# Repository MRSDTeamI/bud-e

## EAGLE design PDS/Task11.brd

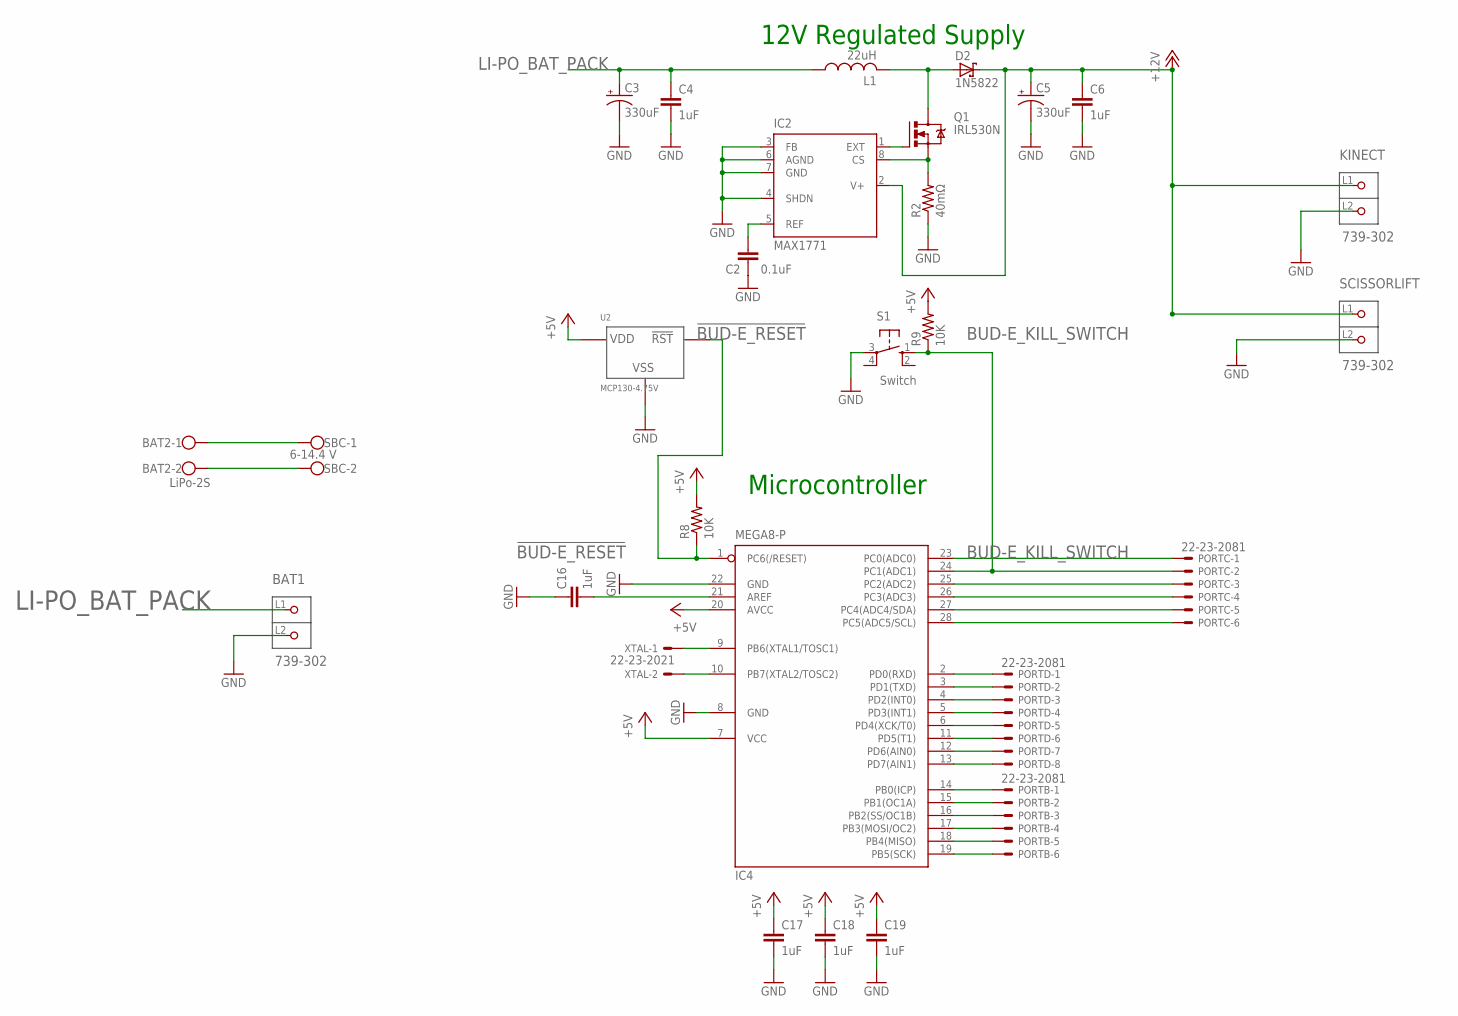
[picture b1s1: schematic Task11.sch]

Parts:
BAT1: 739-302; P-739-302
BAT2: LiPo-2S; W237-113
C2: 0.1uF; C025-025X050
C3, C5: 330uF; E2,5-6
C4, C6, C16, C17, C18, C19: 1uF; C025-025X050
D2: 1N5822; C4111-15
IC2: MAX1771; DIL08
IC4: MEGA8-P; DIL28-3
KINECT: 739-302; P-739-302
L1: 22uH; 0207/15
PORTB: 22-23-2081; 22-23-2061
PORTC: 22-23-2081; 22-23-2061
PORTD: 22-23-2081
Q1: IRL530N; TO220BV
R2: 40mΩ; 0207/12
R8, R9: 10K; 0204/7
S1: Switch; B3F-10XX
SBC: 6-14.4 V; W237-113
SCISSORLIFT: 739-302; P-739-302
U2: MCP130-4.75V; TO92
XTAL: 22-23-2021

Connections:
!BUD-E_RESET: IC4.1 (PC6(/RESET)), R8.1, U2.1 (!RST)
+5V: C17.1, C18.1, C19.1, IC4.7 (VCC), IC4.20 (AVCC), R8.2, R9.2, U2.2 (VDD)
+12V: C5.+, C6.1, D2.C, IC2.2 (V+), KINECT.L1 (P1), SCISSORLIFT.L1 (P1)
BUD-E_KILL_SWITCH: IC4.24 (PC1(ADC1)), PORTC.2, R9.1, S1.1 (S)
GND: BAT1.L2 (P2), C2.1, C3.-, C4.2, C5.-, C6.2, C16.1, C17.2, C18.2, C19.2, IC2.3 (FB), IC2.4 (SHDN), IC2.6 (AGND), IC2.7 (GND), IC4.8 (GND), IC4.22 (GND), KINECT.L2 (P2), R2.1, S1.3, SCISSORLIFT.L2 (P2), U2.3 (VSS)
LI-PO_BAT_PACK: BAT1.L1 (P1), C3.+, C4.1, L1.1
unnamed: IC2.1 (EXT), Q1.G
unnamed: C2.2, IC2.5 (REF)
unnamed: IC2.8 (CS), Q1.S, R2.2
unnamed: IC4.23 (PC0(ADC0)), PORTC.1
unnamed: IC4.25 (PC2(ADC2)), PORTC.3
unnamed: IC4.26 (PC3(ADC3)), PORTC.4
unnamed: D2.A, L1.2, Q1.D
unnamed: IC4.27 (PC4(ADC4/SDA)), PORTC.5
unnamed: IC4.28 (PC5(ADC5/SCL)), PORTC.6
unnamed: IC4.2 (PD0(RXD)), PORTD.1
unnamed: IC4.9 (PB6(XTAL1/TOSC1)), XTAL.1
unnamed: IC4.3 (PD1(TXD)), PORTD.2
unnamed: IC4.4 (PD2(INT0)), PORTD.3
unnamed: IC4.5 (PD3(INT1)), PORTD.4
unnamed: IC4.6 (PD4(XCK/T0)), PORTD.5
unnamed: IC4.11 (PD5(T1)), PORTD.6
unnamed: IC4.12 (PD6(AIN0)), PORTD.7
unnamed: IC4.13 (PD7(AIN1)), PORTD.8
unnamed: IC4.14 (PB0(ICP)), PORTB.1
unnamed: IC4.15 (PB1(OC1A)), PORTB.2
unnamed: IC4.16 (PB2(SS/OC1B)), PORTB.3
unnamed: IC4.17 (PB3(MOSI/OC2)), PORTB.4
unnamed: IC4.18 (PB4(MISO)), PORTB.5
unnamed: IC4.19 (PB5(SCK)), PORTB.6
unnamed: BAT2.1, SBC.1
unnamed: BAT2.2, SBC.2
unnamed: C16.2, IC4.21 (AREF)
unnamed: IC4.10 (PB7(XTAL2/TOSC2)), XTAL.2

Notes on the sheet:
Microcontroller
12V Regulated Supply

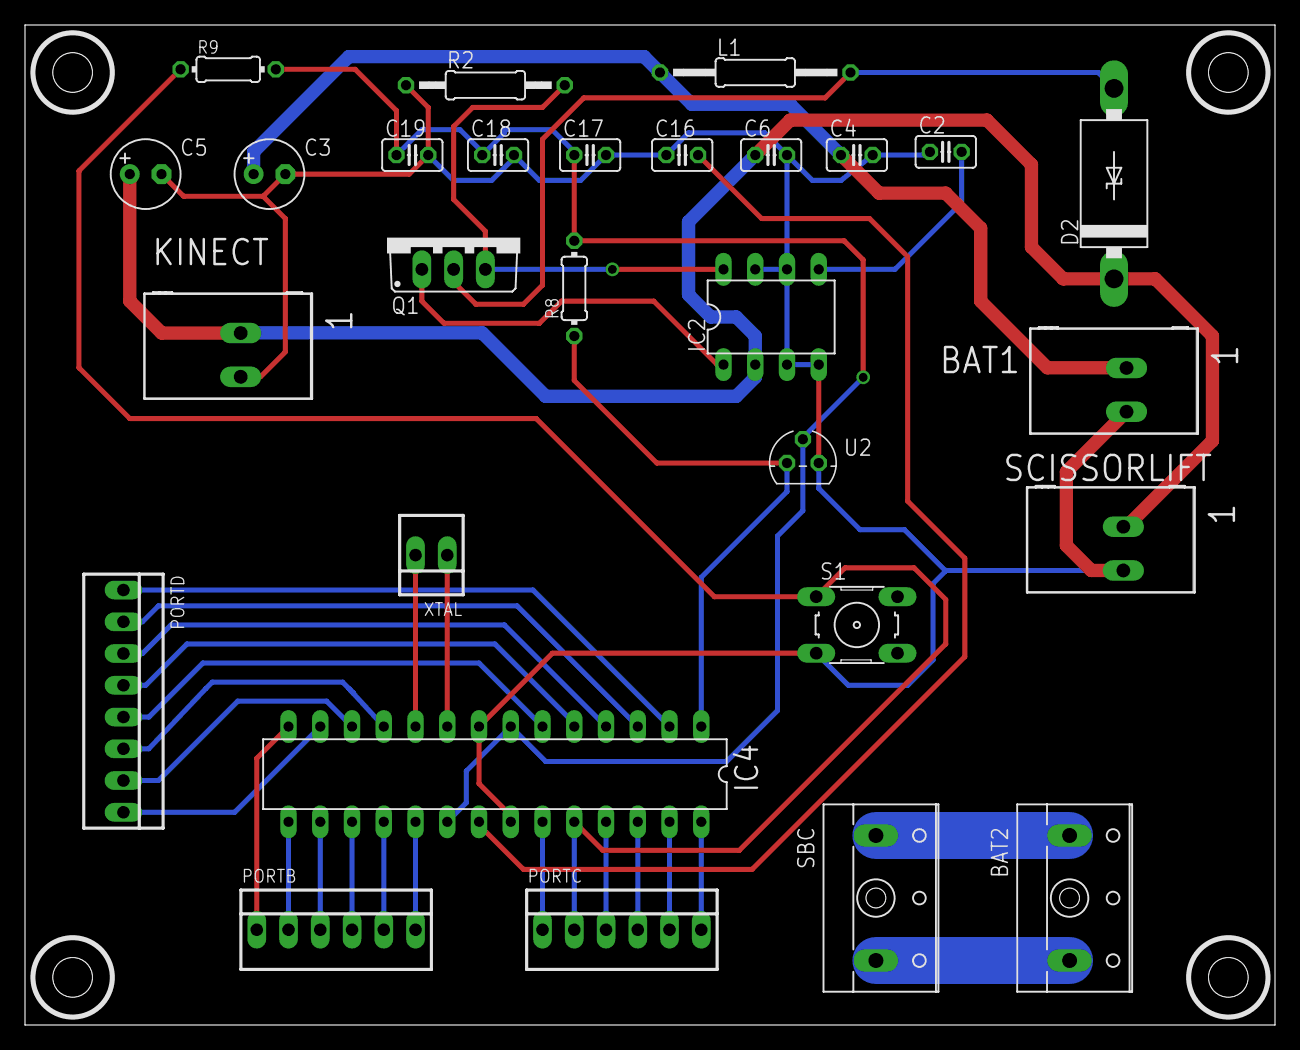
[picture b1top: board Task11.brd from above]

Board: 2 copper layers, 100.0 x 80.0 mm, 28 parts (0 on the bottom side), 34 nets.

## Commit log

2014-11-04 Added final PDS design and documents.
2014-11-04 Initial commit for directory that holds our Arduino code for BUD-E.
2014-11-04 Initial commit for directory that holds our CAD designs for BUD-E.
2014-11-04 Initial commit for directory to hold our ROS code.
2014-11-09 Adding rgbdslam_v2 that worked on my Ubuntu 12.04.5 with Hydro. Note: To get it to compile, had to add this compilation flag in CMakeLists.txt: -march=native -mno-avx
    For more details see http://answers.ros.org/question/190688/rgbdslam-v2-catkin_make-error/#196763
2014-11-09 Adding CCNY SLAM that worked on my Ubuntu 12.04.5 with Hydro.
    Had to make a modification from the CCNY repo:
    1. Commented out all references to SURF in header files because it was removed
    a month ago.
2015-01-13 Added ROS control node for MiniDora
2015-01-13 Added ROS node to control the pioneer Base using RosAria
2015-01-13 Added the rosaria library. It includes binaries built on a x86_64 machine. The main difference between the official distribution is the RosAria node which was modified to remove dependency on the mot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
2015-01-13 Added MiniDora sketch for the Arduino Uno
2015-02-23 Initial check-in for can/bottle detection on a desk. It downsamples the point cloud, segments out planes, clusters points, then prints out the centroid of the cluster.
2015-02-23 Fixed spacing and removed some un-needed comments.
2015-02-23 Added publisher to publish the center coordinates of cluster.
2015-02-24 Adjust parameters in detect_can to filter out noisy data. Commented out normals computation because won't be trying that for cylindrical segmentaiton anytime soon.
2015-02-24 Added new node to parse the cluster centers output by detect_can and filter/average it out so it only spits out a new center coordinate when there are large changes over a duration of time.
2015-03-29 Added README and new detect_cylinder node that specifically parses for cylindrical objects.
2015-03-30 Added Code for BUDe-E's UI subsystem. Also includes the node for integrating UI and Navigation subsystem
2015-03-30 Code to set goals directly to the manipulator without using RVIZ marker is added.
2015-03-31 Code for bude_arm moveit! simulation is added
2015-03-31 bude_arm
2015-03-31 URDF for BUD-E's ARM
2015-04-07 Added latest files for bottle detection algorithm.
2015-04-07 Added header file that detect_cylinder.cpp needs.
2015-04-12 Updated parse_center to output to 'target_height' topic for scissor lift and 'bottle_center' for arm. Changed detect_cylinder.cpp back to its original working state.
2015-04-12 Added subscriber so vision system will not run until it sees 'true' in 'start_vision' topic. It can also shut off when it sees 'false' again. Also removed debug prints.
2015-04-13 Initial check-in for node that moves arm based on coordinates from 'bottle_center' topic.
2015-04-13 Added integrated code so far. Till PR 12
2015-04-15 Added README on how to use/test with jw_budeArmControl.py.
2015-04-15 Modified jw_budeArmControl.py to also take 4 joint values if desired.
2015-04-19 Initial check-in of forward and inverse kinematics. FK has been tested and works. IK runs into problem with singular matrix error after a while when trying to take the inverse matrix.
2015-04-20 Put set_joint_value_target() back in for non-joint value control. Meaning setting j_vals=0 and using x,y,z position.
2015-04-20 Updated IK to use DLS method so we won't get singular matrix with 3 or 4 DoF arm. Updated files to use Crustcrawler arm variables.
2015-04-20 Added matlab files I modified from Zach's to test/play with IK.
2015-04-20 Added functionality to subscribe to ROS topic and use the coordinates from that topic to calculate the IK angle values.
2015-04-20 Updated InverseKin so it will automatically pass the joint values to dynamixel servos after it has calculated all the joint values.
2015-04-20 Updated to use geometric method to calculate first (shoulder_pan) motor angle.
2015-04-20 Added move_home() function where the arm moves to the front of the system pointing down so the vision system can see over it.
2015-04-21 Updated nodes to move the elbow/gripper upward before moving the arm to position. This way we won't hit the bottle with the outside of the gripper as we move side to side. After moving into position 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
2015-04-21 Updated files to work with gripper.
2015-04-21 node update
2015-04-21 Added new dynamixel driver package that Gautam found. This works for us and the "regular" one we downloaded doesn't.
2015-04-21 Initial check-in for launch file that launches freenect (for Indigo), detect_cylinder, and parse_center.
2015-04-21 Updated kinematics to use 4 points (not just calculating up to elbow joint). Also added 5cm to the final wrist joint so we are calculating IK for a point close to middle of the gripper.
2015-04-21 Moved config and launch files into folders for better organization.
2015-04-21 Added Zach's scissor lift code.
2015-04-21 Updated HOME position of arm to the starboard (right) side of the robot.
2015-04-21 Updated home position so it's not as close to the body. Also added flag so arm will always move to an area where it won't hit the base while moving to bottle. Updated copyright.
2015-04-21 Lowered plane segementation threshold to 30% (from 10%) so we can see the bottle in cluttered environment. Also limited width of Kinect's vision (x axis) from -0.5m to 0.5m. Changed parse_center beca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
2015-04-21 Added code to check for 'load' of the gripper motor. This will be our feedback to determine if the bottle has been grasped. Also added algorithm to move arm to the basket and drop the bottle.
    The arm retry has not been fully implemented yet.
    This code has NOT been tested.
2015-04-22 Fixed typo bug with elbow control and made default arm position farther away from base.
2015-04-22 Fixed how we access MotorStateList and added default gripper load value of 7 (may need to be tweaked).
2015-04-22 Inverted y-axis for Kinect to arm conversion b/c y is pointing downward in Kinect's frame.
2015-04-22 Fixed recursion error.
2015-04-22 Updated files to drop bottle into basket
2015-04-22 Changes to correctly pass height value to scissor lift. Some tweaks to where coordinates are for Kinect vs arm.
2015-04-22 Wait before checking load and after grasping. Also added new code to check arm position.
2015-04-22 Arm retry 3 times then tells navigation to go back.
2015-04-22 Updated parse_center so it resets based on reset_parse topic. Updated InverseKin.py so it uses reset_parse to tell parse_center to start over and get new bottle coordinates.
2015-04-22 Blah
2015-04-22 Fixed offset problem
2015-04-22 Fixed publishing retry to parse_center. Updated offsets
2015-04-22 Latest bottle center offsets that works very close to 100% of the time.
2015-04-22 Latest offsets.
2015-04-22 Upped retries to 5 and fixed retry code.
2015-04-22 New offsets.
2015-04-22 Updated README to include instructions for running vision and manipulation system together.
2015-04-25 SVE updates
2015-04-26 Updated arm's 'home' position to be upright and in front when BUD-E is navigating. The arm's home position changes to the right once it 'start_vision' topic is set to true. Also tested retry so the a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
2015-04-28 Added mechanism to disable parse_center while the arm is trying to grasp the bottle. parse_center won't start again until the arm has moved out of the way.
2015-04-28 New scissor lift control code which can accept negative number. And switch from absolute height to relative height(reference from the last command)
2015-04-28 tidied up the fsm node
2015-04-28 Updated Readme file
2015-04-28 Update the Readme file to include all subsystem launch information
2015-04-28 Update readme file
2015-04-28 Updated parse_center to subscribe Int on target_height. This is because arduino code change that allows scissor lift to move up and down using positive and negative numbers.
2015-04-28 Added check so we don't rotate a joint out of range. Sometimes the IK gives joint angles that are out of bounds. We ignore that calculation and retry.
2015-04-28 Some tweaks to detect bottle better when it's on a box.
2015-04-28 Added the fixed RosAria node
2015-04-29 Update arm to reset try counter if it sees reset_arm.
2015-04-29 Set 'start_vision' to False once we start moving back.
2015-04-29 Added check to reset arm only.
2015-04-29 Move retry check to after grasp attempt so we don't have to wait until next time bottle coordinate comes in to check for retry attempts.
2015-04-29 Fixed typos.
2015-09-17 Cleaned up some code. Mostly for manipulation stuff. Mostly documentation.
2015-09-29 Refactored detect_cylinder into a class. Uses the detect_cylinder.h header file and _should_ run the same as regular detect_cylinder.cpp.
